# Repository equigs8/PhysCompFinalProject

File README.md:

# Project Overview

The final project for MTEC 2280_D10 Physical Computing.

See the [Wiki](https://github.com/equigs8/PhysCompFinalProject/wiki) for more information

The goal of the project is to create a gaming handheld with an esp32 board.
# Documentation
## General
[ESP32-S3-DevKitC-1 v1.1](https://docs.espressif.com/projects/esp-dev-kits/en/latest/esp32s3/esp32-s3-devkitc-1/user_guide_v1.1.html#getting-started)

## Graphics/Display
[ArduinoGraphicsLibrary | Arduino Documentation](https://docs.arduino.cc/libraries/arduinographics/)

[Adafruit GFX Library | Arduino Documentation](https://docs.arduino.cc/libraries/adafruit-gfx-library/#Compatibility)

[Introduction — LVGL documentation](https://docs.lvgl.io/8.2/intro/index.html)

# Memory/Storage
[ESP partition API ← we should be careful with this](https://docs.espressif.com/projects/esp-idf/en/stable/esp32s3/api-reference/storage/partition.html)

## Battery
[Battery management system](https://www.adafruit.com/product/4712)

[Adafruit lipoly protection](https://learn.adafruit.com/li-ion-and-lipoly-batteries/protection-circuitry)

## Audio
[AT-1224-TWT-5V-2-R PUI Audio, Inc. | Audio Products | DigiKey](https://www.digikey.com/en/products/detail/pui-audio-inc/AT-1224-TWT-5V-2-R/5011404)

## PCB
[Githhub| espressif Kicad library](https://github.com/espressif/kicad-libraries?tab=readme-ov-file)

# Component List

- ESP32-s3-DevKitC-1
- Buttons x 6
- power switch
- Screen
- Piezo
- Volume slider ← software based
- battery ← 4 AA connected to G & 5V pins?
- Power led
- PCB/protoboard
- Case

[Full assembly.stl](Fullassembly.stl)
[stakeholdermap](StakeholderMap.md)

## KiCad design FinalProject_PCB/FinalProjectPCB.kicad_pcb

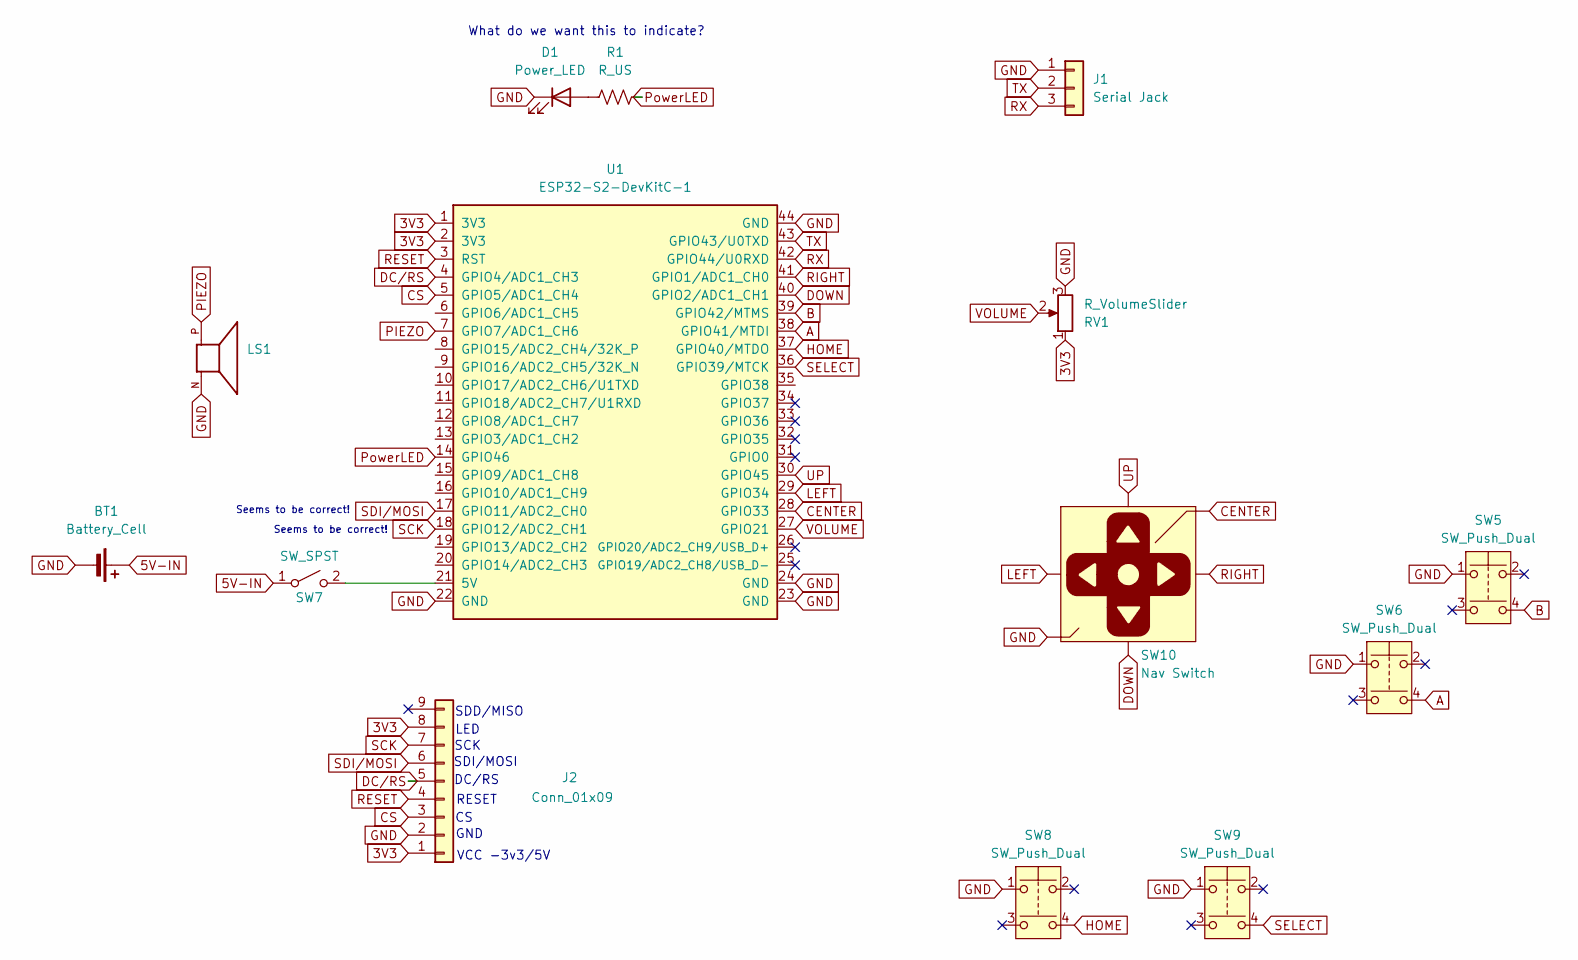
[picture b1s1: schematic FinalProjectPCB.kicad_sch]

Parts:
BT1: Battery_Cell; TerminalBlock_Xinya_XY308-2.54-2P_1x02_P2.54mm_Horizontal
D1: Power_LED; LED_D3.0mm
J1: Serial Jack; TerminalBlock_Xinya_XY308-2.54-3P_1x03_P2.54mm_Horizontal
J2: Conn_01x09; TerminalBlock_Xinya_XY308-2.54-9P_1x09_P2.54mm_Horizontal
LS1: Piezo_XDCR_AT-1224-TWT-5V-2-R
R1: R_US; R_Axial_DIN0204_L3.6mm_D1.6mm_P5.08mm_Horizontal
RV1: R_VolumeSlider; Thumb_TRIM_3352T-1-104LF
SW5, SW6, SW8, SW9: SW_Push_Dual; D6R90_CNK Button
SW7: SW_SPST; TerminalBlock_Xinya_XY308-2.54-2P_1x02_P2.54mm_Horizontal
SW10: Nav Switch; Multi-Directional Switch 5 Position
U1: ESP32-S2-DevKitC-1

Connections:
3V3: J2.1, J2.8, RV1.1, U1.1 (3V3), U1.2 (3V3)
5V-IN: BT1.1 (+), SW7.1 (A)
A: SW6.4, U1.38 (GPIO41/MTDI)
B: SW5.4, U1.39 (GPIO42/MTMS)
CENTER: SW10.4 (Center), U1.28 (GPIO33)
CS: J2.3, U1.5 (GPIO5/ADC1_CH4)
DC/RS: J2.5, U1.4 (GPIO4/ADC1_CH3)
DOWN: SW10.5 (Down), U1.40 (GPIO2/ADC1_CH1)
GND: BT1.2 (-), D1.1 (K), J1.1, J2.2, LS1.N, RV1.3, SW5.1, SW6.1, SW8.1, SW9.1, SW10.3 (GND), SW10.6 (GND), SW10.8 (GND), SW10.9 (GND), SW10.10 (GND), U1.22 (GND), U1.23 (GND), U1.24 (GND), U1.44 (GND)
HOME: SW8.4, U1.37 (GPIO40/MTDO)
LEFT: SW10.7 (Left), U1.29 (GPIO34)
unnamed: D1.2 (A), R1.1
unnamed: SW7.2 (B), U1.21 (5V)
PIEZO: LS1.P, U1.7 (GPIO7/ADC1_CH6)
PowerLED: R1.2, U1.14 (GPIO46)
RESET: J2.4, U1.3 (RST)
RIGHT: SW10.2 (Right), U1.41 (GPIO1/ADC1_CH0)
RX: J1.3, U1.42 (GPIO44/U0RXD)
SCK: J2.7, U1.18 (GPIO12/ADC2_CH1)
SDI/MOSI: J2.6, U1.17 (GPIO11/ADC2_CH0)
SELECT: SW9.4, U1.36 (GPIO39/MTCK)
TX: J1.2, U1.43 (GPIO43/U0TXD)
UP: SW10.1 (Up), U1.30 (GPIO45)
VOLUME: RV1.2, U1.27 (GPIO21)

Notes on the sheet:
GND
SDI/MOSI
Seems to be correct!
LED
DC/RS
SCK
VCC -3v3/5V
SDD/MISO
What do we want this to indicate?
RESET

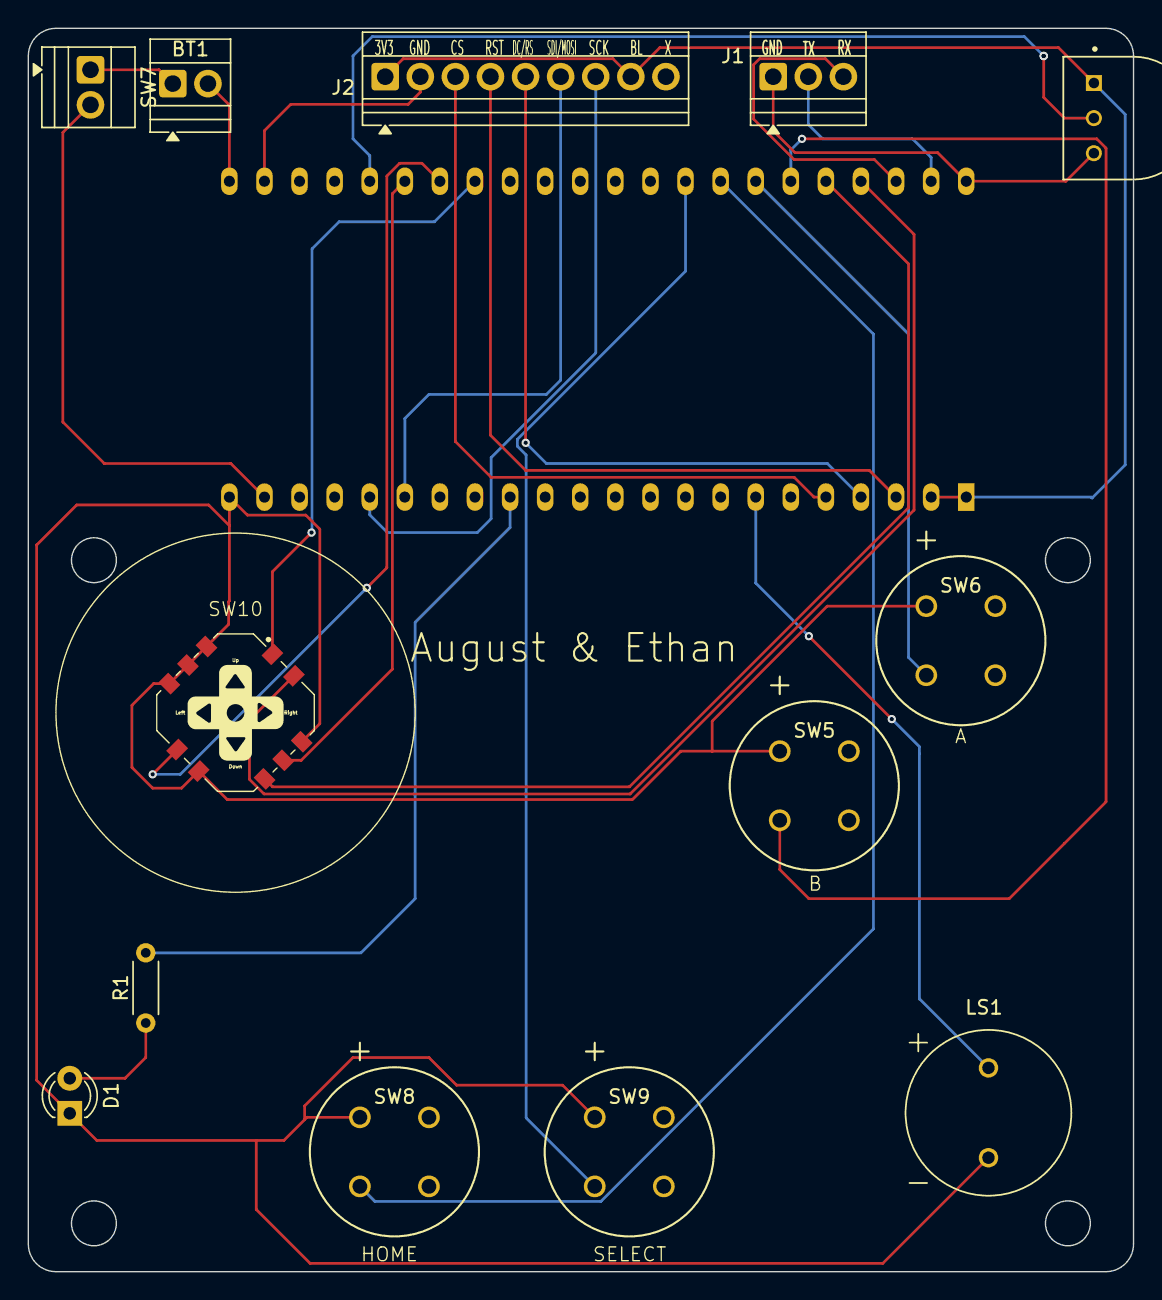
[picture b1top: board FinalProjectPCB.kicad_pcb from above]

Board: 2 copper layers, 80.0 x 90.0 mm, 14 parts (1 on the bottom side), 24 nets.

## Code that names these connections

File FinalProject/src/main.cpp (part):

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#define PIN_LEFT   48
#define PIN_RIGHT  1
#define PIN_SELECT 16
#define PIN_HOME   40
#define PIN_BUTTONA 41
#define PIN_BUTTONB 17

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// #define PIN_LEFT   102
// #define PIN_RIGHT  103
// #define PIN_SELECT 104
// #define PIN_HOME   105
// #define PIN_BUTTONA 18
// #define PIN_BUTTONB 107

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//#define PIN_POWER_INDICATOR 46

// Volume Control
//#define PIN_VOLUME 8
//#define PIN_PIEZO 7

// ==============================================================================
// 2. DISPLAY SETUP & GLOBAL VARIABLES
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int currentVolume = 128;

void initAudio() {
  //ledcAttach(PIN_PIEZO, 2000, AUDIO_RESOLUTION);
  //ledcWrite(PIN_PIEZO, 0);
}

void updateVolume(){
  // int potValue = analogRead(PIN_VOLUME);
  // int mappedValue = map(potValue, 0, 4095, 0, 128);

  // currentVolume = (mappedValue * mappedValue) / 128;
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  // updateVolume();

  // if(currentVolume > 0 && freq > 0){
  //   ledcWriteTone(PIN_PIEZO, freq);
    
  //   ledcWrite(PIN_PIEZO, currentVolume);

  //   delay(duration);
  //   ledcWrite(PIN_PIEZO, 0);
  // }
}

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  // Handle Home Button
  if(currentTime - lastMoveTime >= moveDelay){
    bool moved = false;
    if(digitalRead(PIN_HOME) == LOW) {
      Serial.println("Home Button Pressed");
      moved = true;
      goHome();
    }
    // Handle Reset. Pushing both Home and Select will reset the divice
    
    if(digitalRead(PIN_HOME) == LOW && digitalRead(PIN_SELECT) == LOW) {
      //ESP.restart();
    }

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      Serial.println("Select Pressed");
      moved = true;
    }
    if(digitalRead(PIN_HOME) == LOW) {
      Serial.println("Home Button Pressed");
      moved = true;
    }
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int previousSettingsMenuSelection = 0;
int settingsMenuSelection = 0;
int numSettingsMenu = 2;
const char* settingsMenu[2] = {"Volume", "Coming Soon..."};


void drawSettingsMenuCursor(int previousSelection, int currentSelection){
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  pinMode(PIN_LEFT, INPUT_PULLUP);
  pinMode(PIN_RIGHT, INPUT_PULLUP);
  pinMode(PIN_SELECT, INPUT_PULLUP);
  pinMode(PIN_HOME, INPUT_PULLUP);
  pinMode(PIN_BUTTONA, INPUT_PULLUP);
  pinMode(PIN_BUTTONB, INPUT_PULLUP);

  // Volume potentiometer
  // pinMode(PIN_VOLUME, INPUT);
  // pinMode(PIN_PIEZO, OUTPUT);
  //initAudio();
  // Start the device in the main menu
  tft.fillScreen(MAIN_MENU_COLOR);
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
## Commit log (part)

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2025-11-12 p5js project created
2025-11-12 Arduino ino file
2025-11-12 added git ignore and Arduino files
2025-11-13 Added PCB files
    also fixed duplicate Arduino files
2025-11-13 added Devboard to kicad
2025-11-13 added components
2025-11-13 added Piezo
2025-11-13 added volume slider
2025-11-13 Simple tik tac toe game
2025-11-13 removed unnecessary python script
2025-11-13 tagged all components
2025-11-13 fixed button wiring
2025-11-13 added some footprints
2025-11-14 main menu work
2025-11-14 new tiktaktoe logo
2025-11-14 added backlight options
2025-11-15 Fixed logo problem
2025-11-15 game over splash screen. A Button now implemented.
2025-11-17 keyboard input support
2025-11-17 Early Pokemon menu
2025-11-17 updated pins
2025-11-19 tictactoe cursor fix and diagram wiring
2025-11-19 added GND pin to serial
2025-11-19 updated work.
2025-11-21 Pokemon UI finished + sprites
2025-11-21 pokemon updates
2025-11-23 Main combat loop + colored sprites + classes
2025-11-23 pokeball sprite
2025-11-26 Work on Chess game
2025-11-26 fixing chess menu cursor
2025-11-26 chess board
2025-12-03 Updated Schematic to match working board
2025-12-03 chess pieces class
2025-12-04 added footprints
2025-12-04 Started PCB
2025-12-05 Finished PCB
2025-12-06 white pieces implemented
2025-12-06 black pieces
2025-12-06 added 3d Model
2025-12-08 chess end game
2025-12-09 chess side ui
2025-12-10 wireless chess. Not tested/functioning
2025-12-10 removed serial and wifi
2025-12-13 Serial WIP
2025-12-13 added selectable settings
2025-12-14 main menu cursor center
2025-12-14 removed WIFI include
2025-12-14 Piezo pin
2025-12-14 Icons.h separate file
2025-12-14 header
2025-12-14 audio started. Volume WIP
2025-12-15 docstring and volume updates
2025-12-16 left justified menu
2025-12-17 More Pokemon
2025-12-17 in progress
2025-12-17 final push
2025-12-18 added full case assembly
2025-12-19 Chess Fix
2025-12-19 Power Point
2026-01-27 Pin changes
